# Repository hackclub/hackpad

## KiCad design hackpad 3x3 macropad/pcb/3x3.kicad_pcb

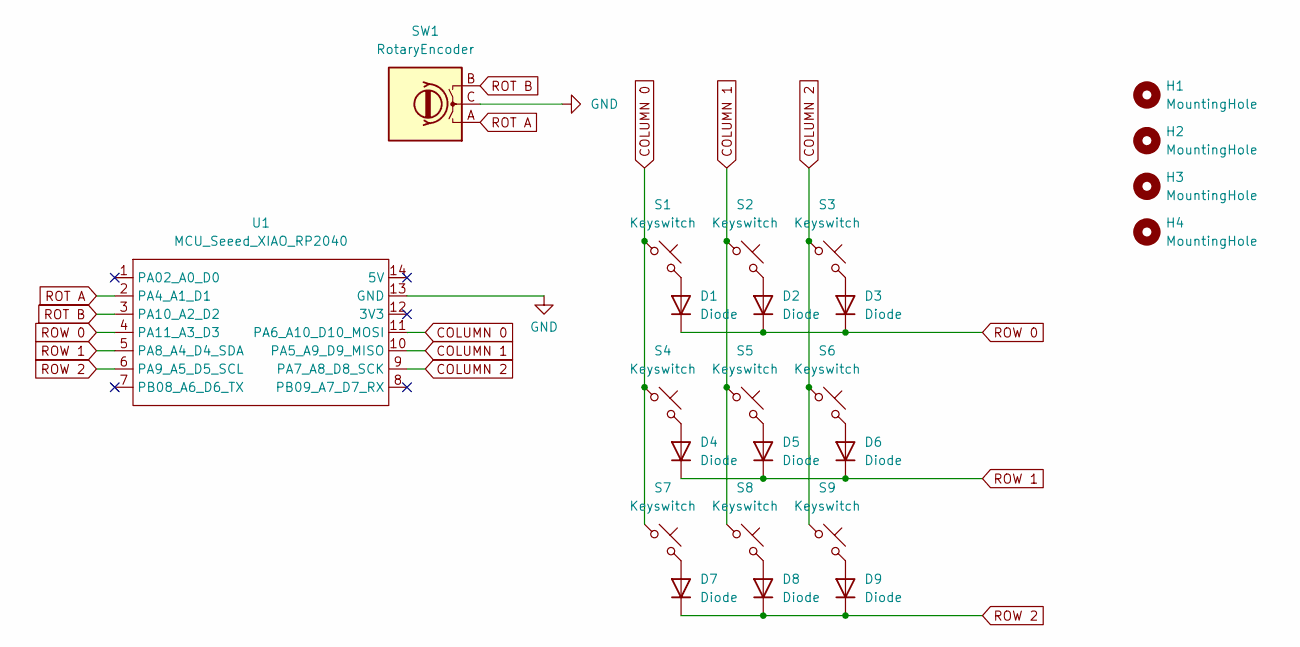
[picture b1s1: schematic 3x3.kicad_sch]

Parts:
D1, D2, D3, D4, D5, D6, D7, D8, D9: Diode; Diode_DO-35
H1, H2, H3, H4: MountingHole; MountingHole_3.5mm
S1, S2, S3, S4, S5, S6, S7, S8, S9: Keyswitch; MX_PCB_1.00u
SW1: RotaryEncoder; RotaryEncoder_Alps_EC11E-Switch_Vertical_H20mm
U1: MCU_Seeed_XIAO_RP2040; Seeed_XIAO_RP2040

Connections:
COLUMN 0: S1.1, S4.1, S7.1, U1.11 (PA6_A10_D10_MOSI)
COLUMN 1: S2.1, S5.1, S8.1, U1.10 (PA5_A9_D9_MISO)
COLUMN 2: S3.1, S6.1, S9.1, U1.9 (PA7_A8_D8_SCK)
GND: SW1.C, U1.13 (GND)
unnamed: D1.2 (A), S1.2
unnamed: D2.2 (A), S2.2
unnamed: D3.2 (A), S3.2
unnamed: D4.2 (A), S4.2
unnamed: D5.2 (A), S5.2
unnamed: D6.2 (A), S6.2
unnamed: D7.2 (A), S7.2
unnamed: D8.2 (A), S8.2
unnamed: D9.2 (A), S9.2
ROT A: SW1.A, U1.2 (PA4_A1_D1)
ROT B: SW1.B, U1.3 (PA10_A2_D2)
ROW 0: D1.1 (K), D2.1 (K), D3.1 (K), U1.4 (PA11_A3_D3)
ROW 1: D4.1 (K), D5.1 (K), D6.1 (K), U1.5 (PA8_A4_D4_SDA)
ROW 2: D7.1 (K), D8.1 (K), D9.1 (K), U1.6 (PA9_A5_D5_SCL)

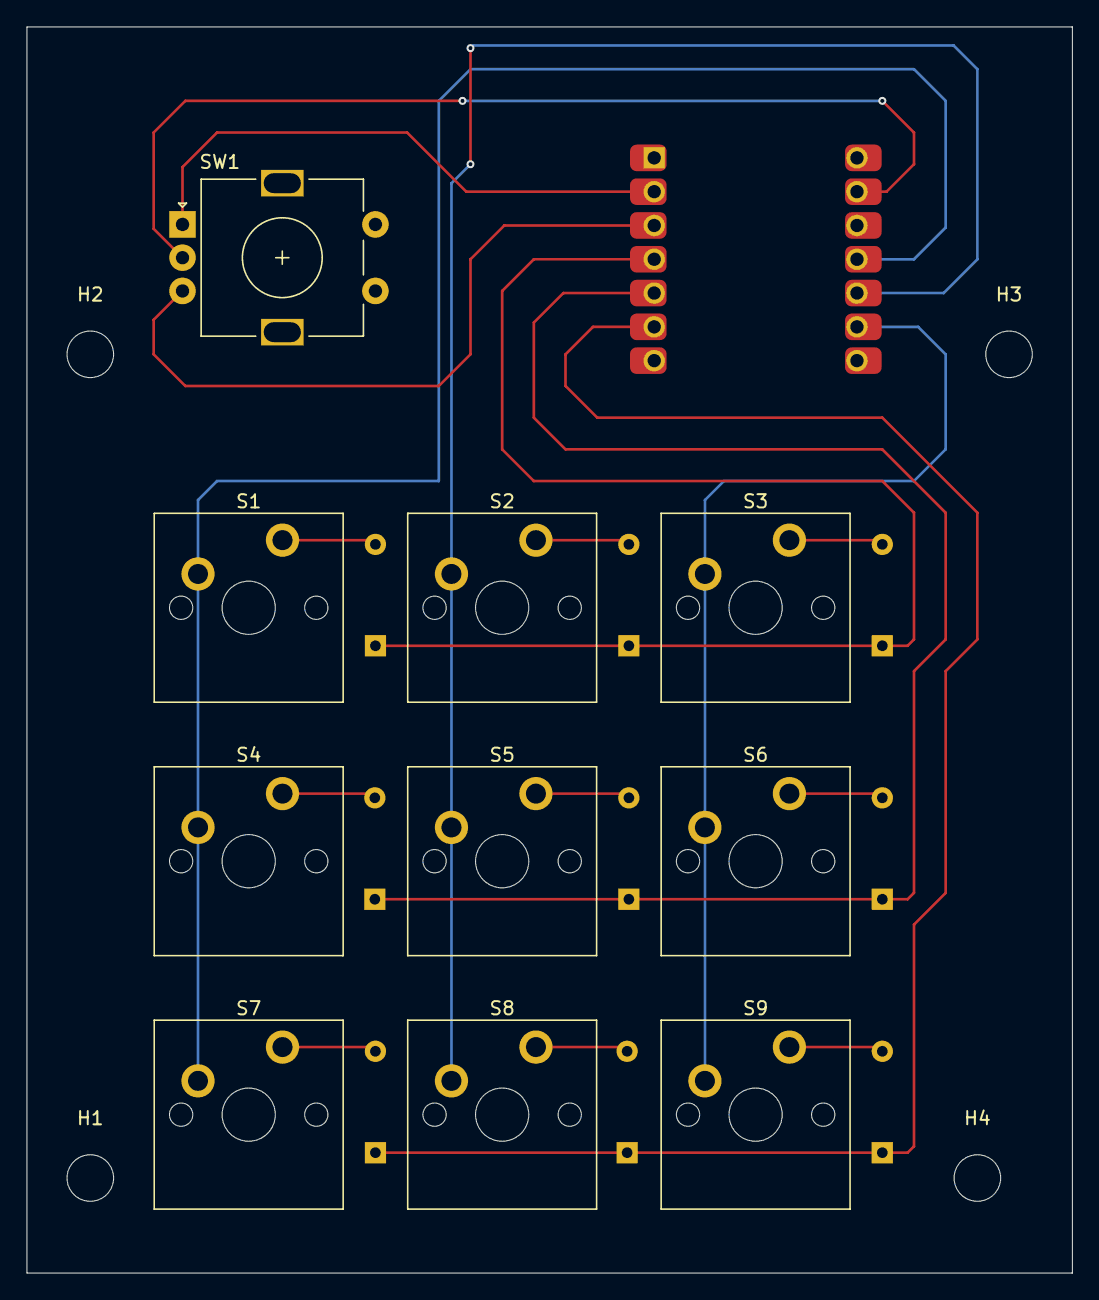
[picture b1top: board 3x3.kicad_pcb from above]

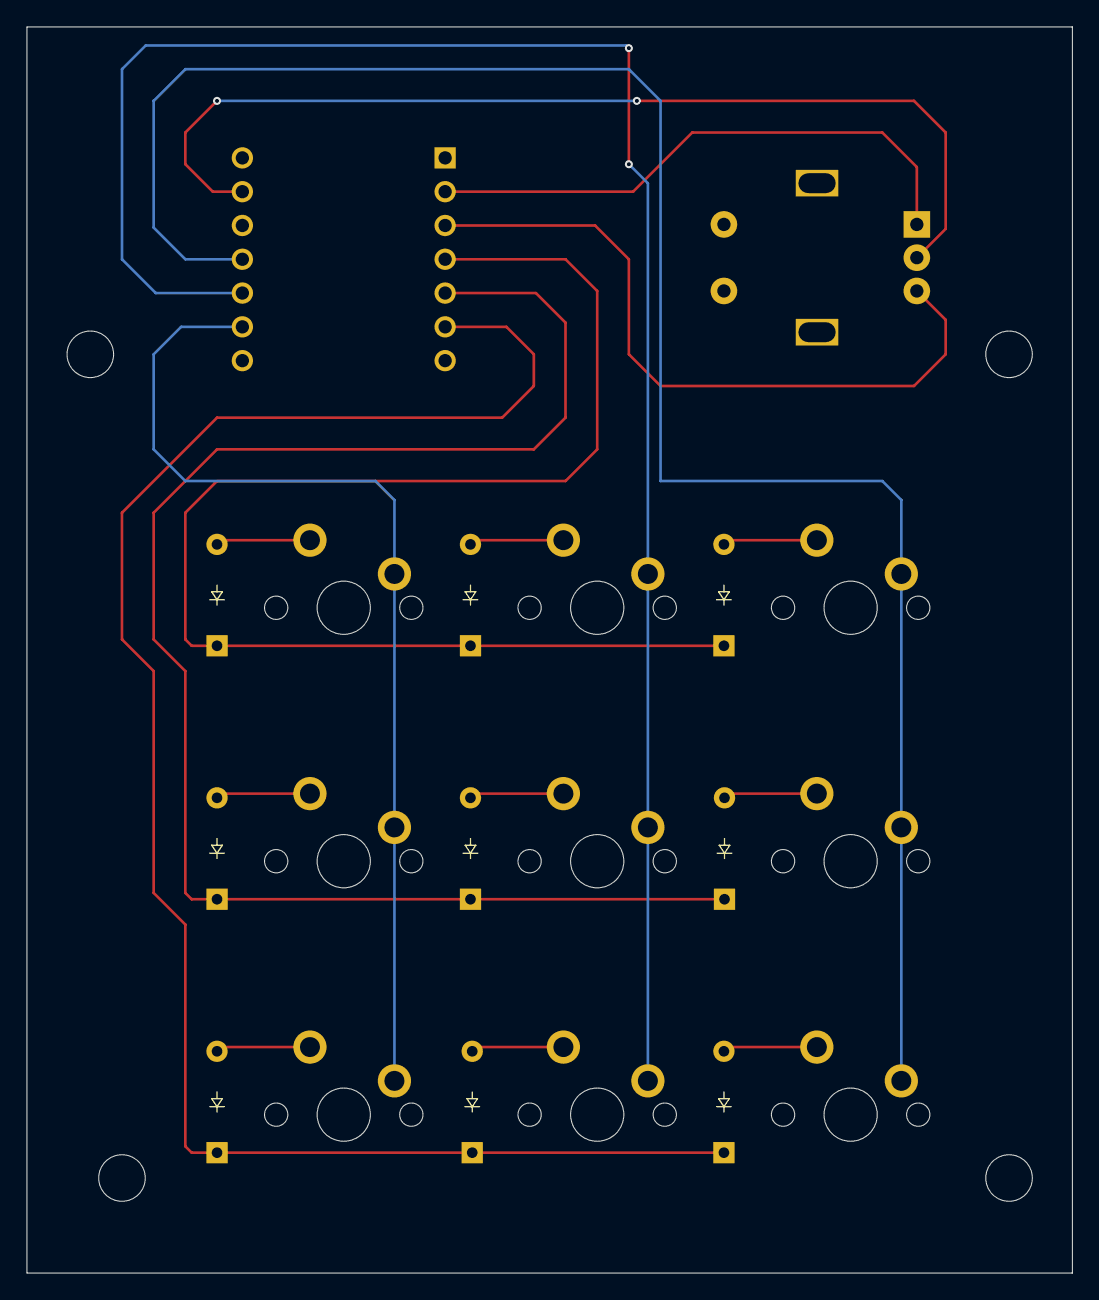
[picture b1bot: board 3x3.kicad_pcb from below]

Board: 2 copper layers, 78.6 x 93.7 mm, 24 parts (9 on the bottom side), 18 nets.

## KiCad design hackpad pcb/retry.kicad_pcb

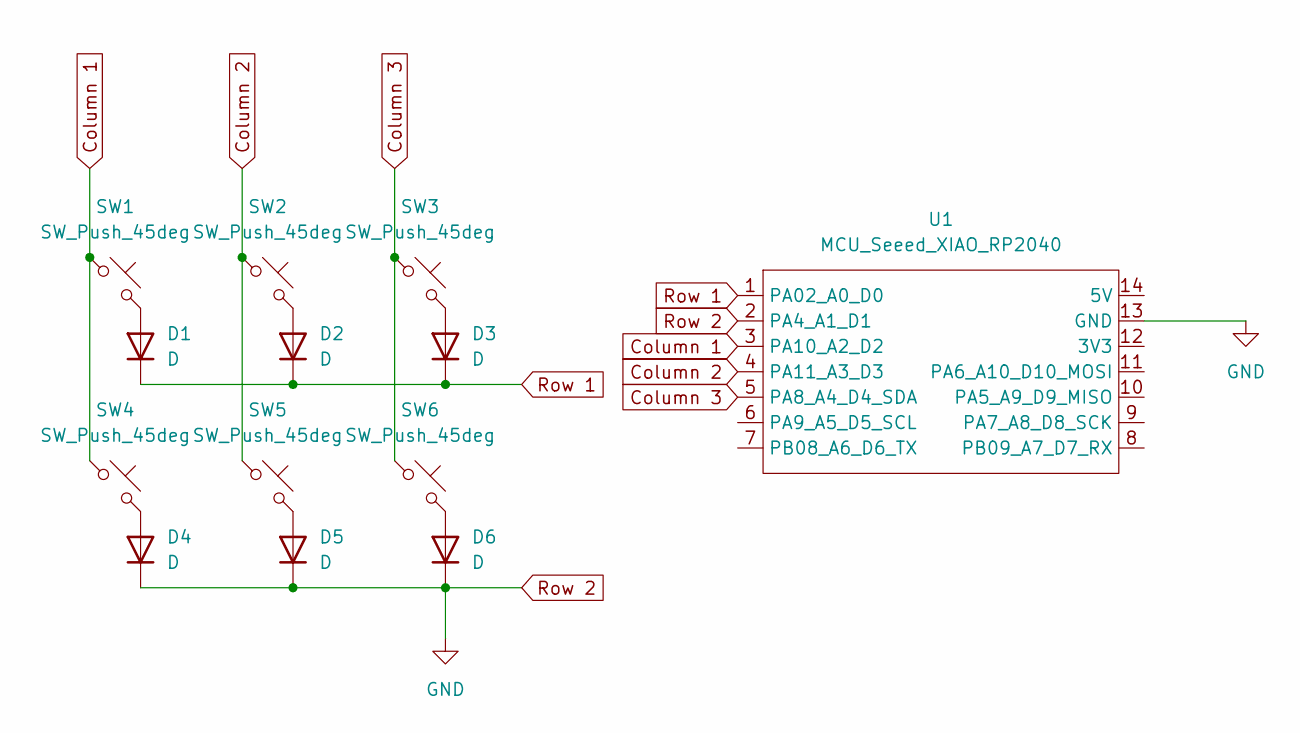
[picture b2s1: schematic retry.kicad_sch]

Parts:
D1, D2, D3, D4, D5, D6: D; Diode_DO-35
SW1, SW2, SW3, SW4, SW5, SW6: SW_Push_45deg; MX_PCB_1.00u
U1: MCU_Seeed_XIAO_RP2040; Seeed_XIAO_RP2040

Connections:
Column 1: SW1.1, SW4.1, U1.3 (PA10_A2_D2)
Column 2: SW2.1, SW5.1, U1.4 (PA11_A3_D3)
Column 3: SW3.1, SW6.1, U1.5 (PA8_A4_D4_SDA)
unnamed: D1.2 (A), SW1.2
unnamed: D2.2 (A), SW2.2
unnamed: D3.2 (A), SW3.2
unnamed: D4.2 (A), SW4.2
unnamed: D5.2 (A), SW5.2
unnamed: D6.2 (A), SW6.2
Row 1: D1.1 (K), D2.1 (K), D3.1 (K), U1.1 (PA02_A0_D0)
Row 2: D4.1 (K), D5.1 (K), D6.1 (K), U1.2 (PA4_A1_D1), U1.13 (GND)

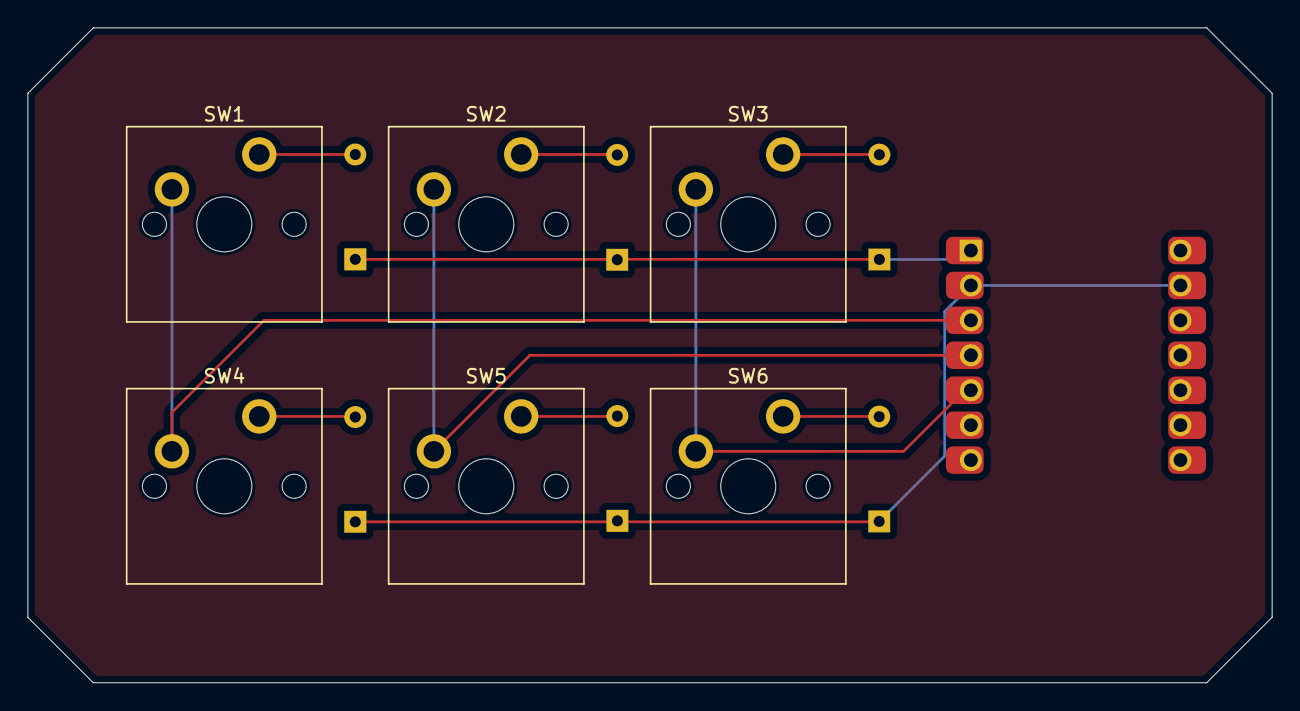
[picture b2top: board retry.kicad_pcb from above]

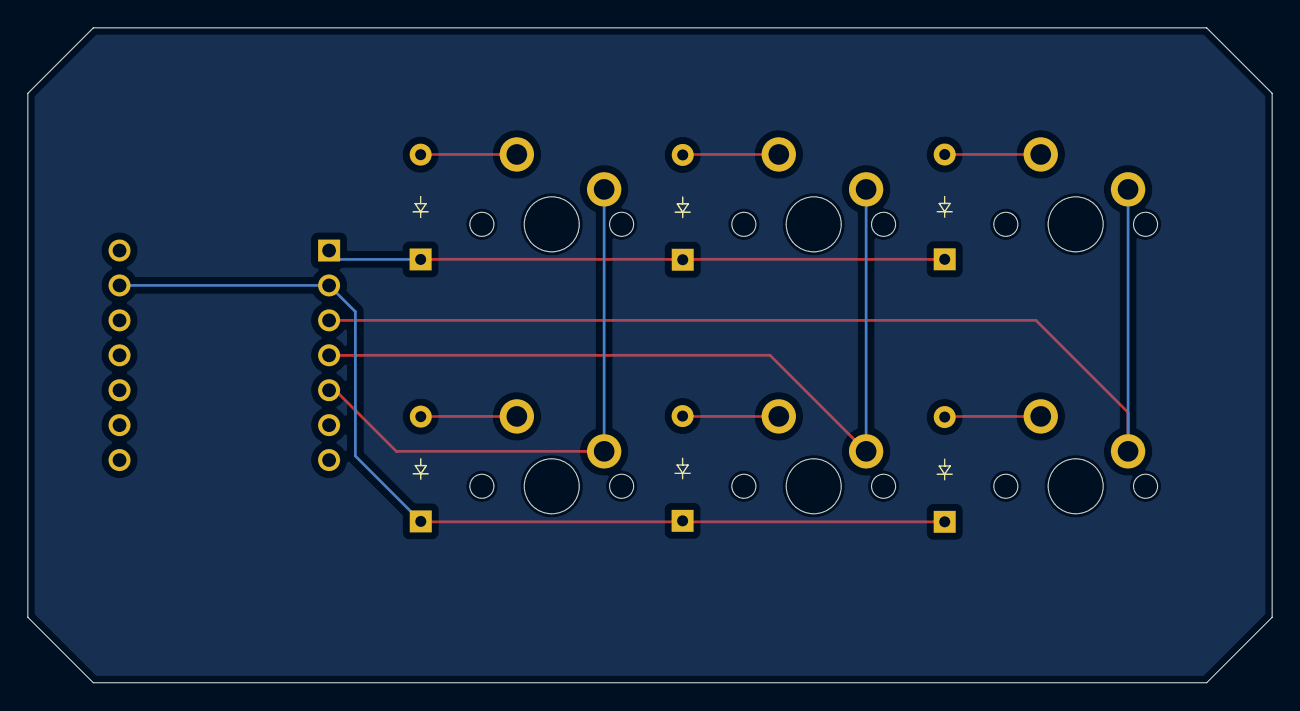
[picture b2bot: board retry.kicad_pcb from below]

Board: 2 copper layers, 90.5 x 47.6 mm, 13 parts (6 on the bottom side), 11 nets.

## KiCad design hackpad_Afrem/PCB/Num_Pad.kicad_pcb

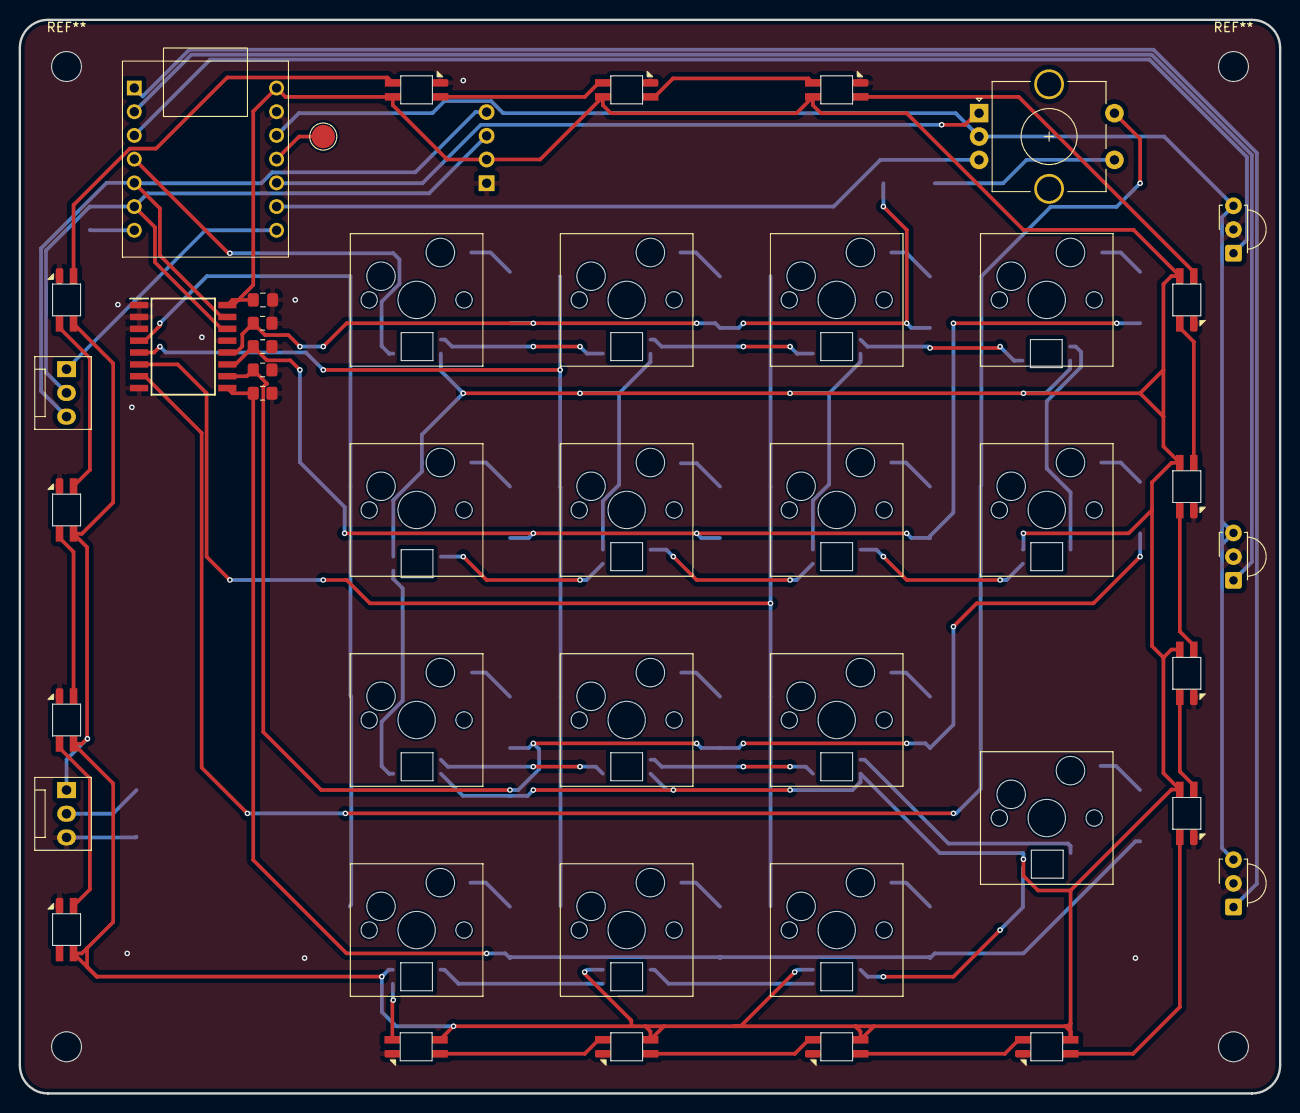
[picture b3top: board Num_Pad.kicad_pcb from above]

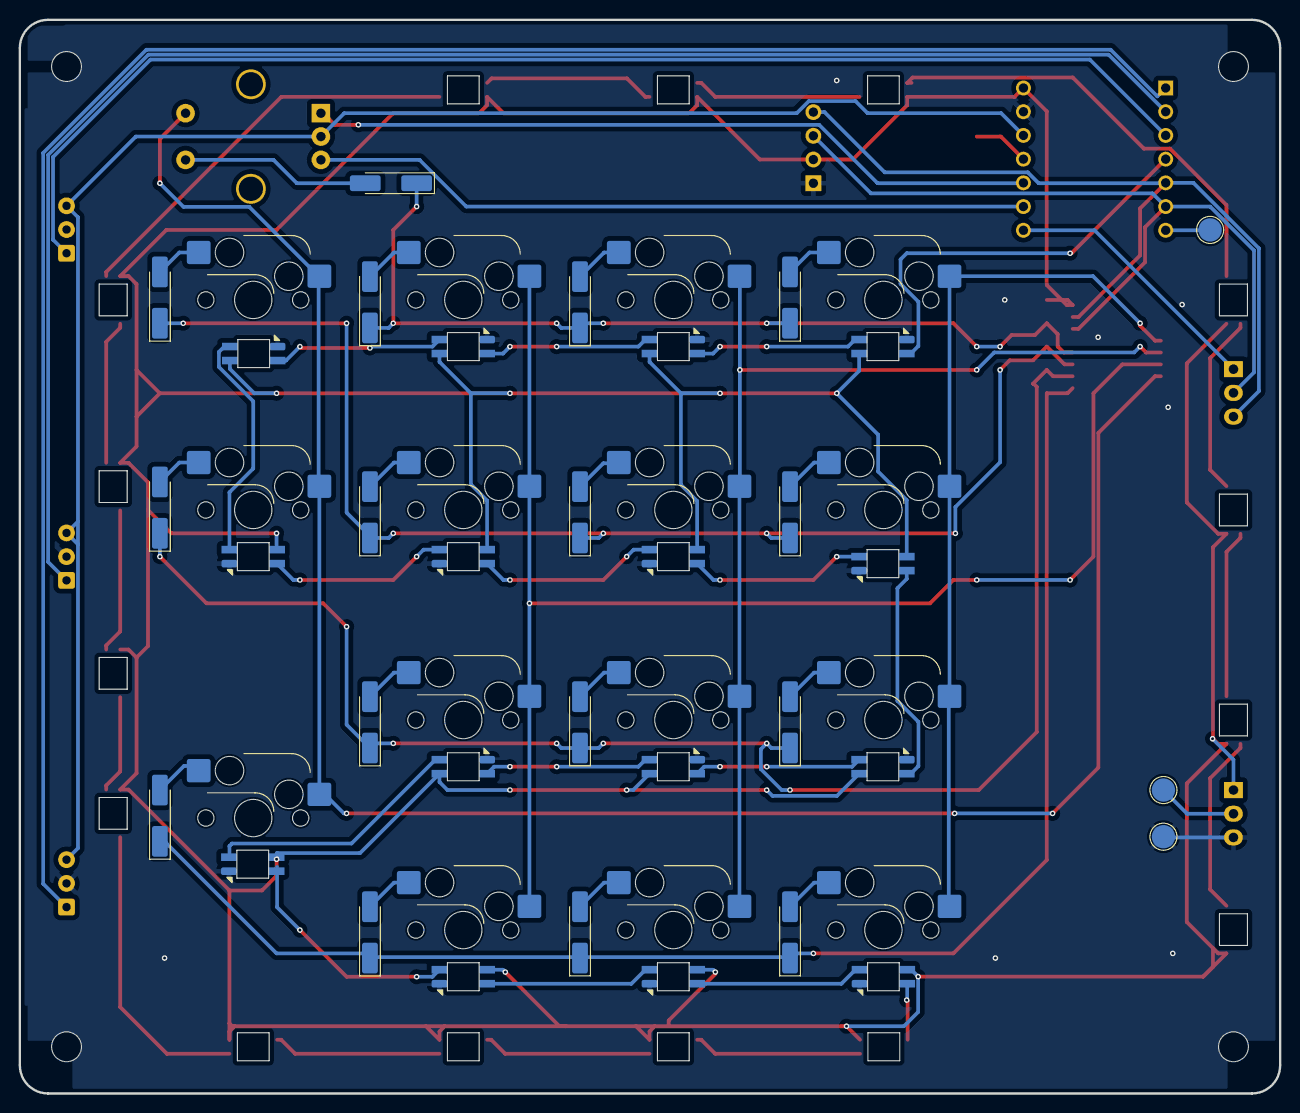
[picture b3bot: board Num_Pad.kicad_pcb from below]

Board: 2 copper layers, 135.0 x 115.0 mm, 79 parts (34 on the bottom side), 68 nets.

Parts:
C1: 100n; C_0805_2012Metric_Pad1.18x1.45mm_HandSolder
D1, D2, D3, D4, D5, D6, D7, D8, D9, D10, D11, D12, D13, D14, D15, D16: Diode; D_MiniMELF_Handsoldering
D19, D20, D21, D22, D23, D24, D25, D26, D27, D28, D29, D30, D31, D32, D33, D34, D35, D36, D37, D38, D39, D40, D41, D42, D43, D44, D45, D46, D47, D48: WS2812B; LED_SK6812MINI
IC1: PCF8574T_3,518; SOIC127P1032X265-16N
J1: OLED_128x32
J3: Data; FanPinHeader_1x03_P2.54mm_Vertical
J4: Spannungsversorgung; FanPinHeader_1x03_P2.54mm_Vertical
R1, R2, R3, R4: 1k; R_0805_2012Metric_Pad1.20x1.40mm_HandSolder
S1: 1; SW_Hotswap_Kailh_MX_1.00u
S2: 2; SW_Hotswap_Kailh_MX_1.00u
S3: 3; SW_Hotswap_Kailh_MX_1.00u
S5: 4; SW_Hotswap_Kailh_MX_1.00u
S6: 5; SW_Hotswap_Kailh_MX_1.00u
S7: 6; SW_Hotswap_Kailh_MX_1.00u
S8: +; SW_Hotswap_Kailh_MX_1.00u
S9: 7; SW_Hotswap_Kailh_MX_1.00u
S10: 8; SW_Hotswap_Kailh_MX_1.00u
S11: 9; SW_Hotswap_Kailh_MX_1.00u
S12: -; SW_Hotswap_Kailh_MX_1.00u
S13: 0; SW_Hotswap_Kailh_MX_1.00u
S14: *; SW_Hotswap_Kailh_MX_1.00u
S15: /; SW_Hotswap_Kailh_MX_1.00u
S16: ENTER; SW_Hotswap_Kailh_MX_2.25u_90deg
SW1: RotaryEncoder_Switch; RotaryEncoder_Alps_EC11E-Switch_Vertical_H20mm_CircularMoun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
TP1, TP2, TP3, TP4: TestPoint; TestPoint_Pad_D2.5mm
U1: MOUDLE-SEEEDUINO-XIAO; MOUDLE14P-2.54-21X17.8MM
U2, U3, U5: TSSP58P38; Vishay_MINICAST-3Pin

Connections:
30kHz: U1.1 (PA02_A0_D0), U2.1 (OUT)
36kHz: U1.2 (PA4_A1_D1), U3.1 (OUT)
56kHz: U1.3 (PA10_A2_D2), U5.1 (OUT)
+3.3V: SW1.C, U1.12 (3V3), U2.3 (Vs), U3.3 (Vs), U5.3 (Vs)
+5V: C1.1, D19.1 (VDD), D20.1 (VDD), D21.1 (VDD), D22.1 (VDD), D23.1 (VDD), D24.1 (VDD), D25.1 (VDD), D26.1 (VDD), D27.1 (VDD), D28.1 (VDD), D29.1 (VDD), D30.1 (VDD), D31.1 (VDD), D32.1 (VDD), D33.1 (VDD), D34.1 (VDD), D35.1 (VDD), D36.1 (VDD), D37.1 (VDD), D38.1 (VDD), D39.1 (VDD), D40.1 (VDD), D41.1 (VDD), D42.1 (VDD), D43.1 (VDD), D44.1 (VDD), D45.1 (VDD), D46.1 (VDD), D47.1 (VDD), D48.1 (VDD), IC1.16 (VDD), J1.2 (VCC), J4.1, U1.14 (5V)
A: SW1.A, U1.10 (PA5_A9_D9_MISO)
B: SW1.B, U1.9 (PA7_A8_D8_SCK)
Col1: IC1.4 (P0), S1.1, S5.1, S9.1, S13.1
Col2: IC1.5 (P1), S2.1, S6.1, S10.1, S14.1
Col3: IC1.6 (P2), S3.1, S7.1, S11.1, S15.1
Col4: IC1.7 (P3), S8.1, S12.1, S16.1, SW1.S2
DIN: D19.4 (DIN), U1.4 (PA11_A3_D3)
GND: C1.2, D19.3 (VSS), D20.3 (VSS), D21.3 (VSS), D22.3 (VSS), D23.3 (VSS), D24.3 (VSS), D25.3 (VSS), D26.3 (VSS), D27.3 (VSS), D28.3 (VSS), D29.3 (VSS), D30.3 (VSS), D31.3 (VSS), D32.3 (VSS), D33.3 (VSS), D34.3 (VSS), D35.3 (VSS), D36.3 (VSS), D37.3 (VSS), D38.3 (VSS), D39.3 (VSS), D40.3 (VSS), D41.3 (VSS), D42.3 (VSS), D43.3 (VSS), D44.3 (VSS), D45.3 (VSS), D46.3 (VSS), D47.3 (VSS), D48.3 (VSS), IC1.1 (A0), IC1.2 (A1), IC1.3 (A2), IC1.8 (VSS), IC1.13 (~INT), J1.1 (GND), J4.3, R1.2, R2.1, R3.2, R4.2, TP1.1, U1.13 (GND), U2.2 (GND), U3.2 (GND), U5.2 (GND)
unnamed: D1.2 (A), S1.2
unnamed: D2.2 (A), S2.2
unnamed: D3.2 (A), S3.2
unnamed: D4.2 (A), SW1.S1
unnamed: D5.2 (A), S5.2
unnamed: D6.2 (A), S6.2
unnamed: D7.2 (A), S7.2
unnamed: D8.2 (A), S8.2
unnamed: D9.2 (A), S9.2
unnamed: D10.2 (A), S10.2
unnamed: D11.2 (A), S11.2
unnamed: D12.2 (A), S12.2
unnamed: D13.2 (A), S13.2
unnamed: D14.2 (A), S14.2
unnamed: D15.2 (A), S15.2
unnamed: D16.2 (A), S16.2
unnamed: D19.2 (DOUT), D20.4 (DIN)
unnamed: D20.2 (DOUT), D21.4 (DIN)
unnamed: D21.2 (DOUT), D22.4 (DIN)
unnamed: D22.2 (DOUT), D23.4 (DIN)
unnamed: D23.2 (DOUT), D24.4 (DIN)
unnamed: D24.2 (DOUT), D25.4 (DIN)
unnamed: D25.2 (DOUT), D26.4 (DIN)
unnamed: D26.2 (DOUT), D27.4 (DIN)
unnamed: D27.2 (DOUT), D28.4 (DIN)
unnamed: D28.2 (DOUT), D29.4 (DIN)
unnamed: D29.2 (DOUT), D30.4 (DIN)
unnamed: D30.2 (DOUT), D31.4 (DIN)
unnamed: D31.2 (DOUT), D32.4 (DIN)
unnamed: D32.2 (DOUT), D33.4 (DIN)
unnamed: D33.2 (DOUT), D34.4 (DIN)
unnamed: D34.2 (DOUT), D35.4 (DIN)
unnamed: D35.2 (DOUT), D36.4 (DIN)
unnamed: D36.2 (DOUT), D37.4 (DIN)
unnamed: D37.2 (DOUT), D38.4 (DIN)
unnamed: D38.2 (DOUT), D39.4 (DIN)
unnamed: D39.2 (DOUT), D40.4 (DIN)
unnamed: D40.2 (DOUT), D41.4 (DIN)
unnamed: D41.2 (DOUT), D42.4 (DIN)
unnamed: D42.2 (DOUT), D43.4 (DIN)
unnamed: D43.2 (DOUT), D44.4 (DIN)
unnamed: D44.2 (DOUT), D45.4 (DIN)
unnamed: D45.2 (DOUT), D46.4 (DIN)
unnamed: D46.2 (DOUT), D47.4 (DIN)
unnamed: D47.2 (DOUT), D48.4 (DIN)
unnamed: J4.2, TP3.1
unnamed: TP2.1, U1.11 (PA6_A10_D10_MOSI)
unnamed: TP4.1, U1.7 (PB08_A6_D6_TX)
Row 1: D1.1 (K), D2.1 (K), D3.1 (K), D4.1 (K), IC1.12 (P7), R1.1
Row 2: D5.1 (K), D6.1 (K), D7.1 (K), D8.1 (K), IC1.11 (P6), R2.2
Row 3: D9.1 (K), D10.1 (K), D11.1 (K), D12.1 (K), IC1.10 (P5), R3.1
Row 4: D13.1 (K), D14.1 (K), D15.1 (K), D16.1 (K), IC1.9 (P4), R4.1
SCL: IC1.14 (SCL), J1.3 (SCL), J3.2, U1.6 (PA9_A5_D5_SCL)
SDA: IC1.15 (SDA), J1.4 (SDA), J3.3, U1.5 (PA8_A4_D4_SDA)
con: J3.1, U1.8 (PB09_A7_D7_RX)

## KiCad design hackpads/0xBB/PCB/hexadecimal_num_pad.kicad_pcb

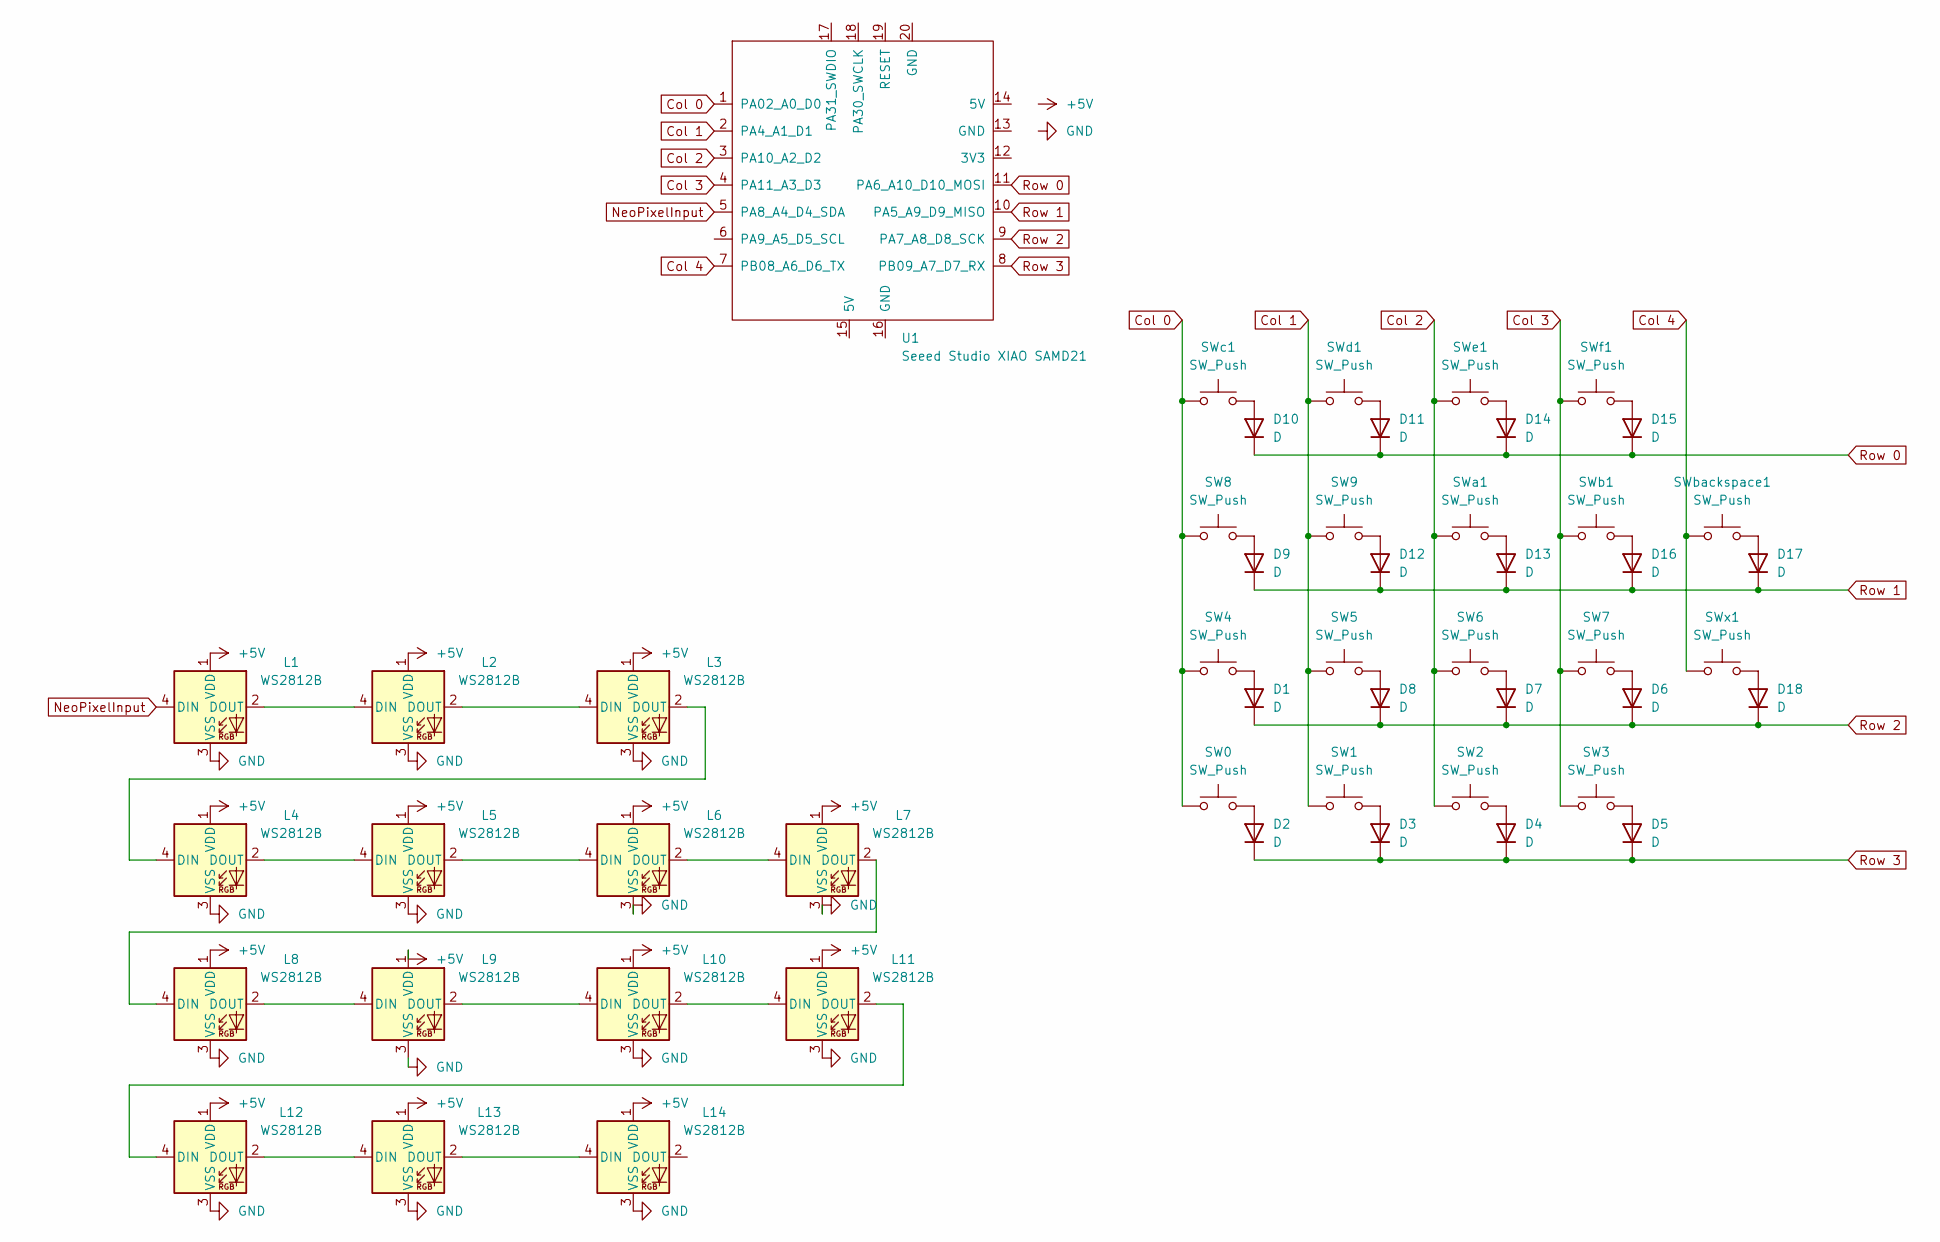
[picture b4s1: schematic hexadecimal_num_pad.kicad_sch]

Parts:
D1, D2, D3, D4, D5, D6, D7, D8, D9, D10, D11, D12, D13, D14, D15, D16, D17, D18: D; D_DO-35_SOD27_P7.62mm_Horizontal
L1, L2, L3, L4, L5, L6, L7, L8, L9, L10, L11, L12, L13, L14: WS2812B; LED_WS2812B_PLCC4_5.0x5.0mm_P3.2mm
SW0, SW1, SW2, SW3, SW4, SW5, SW6, SW7, SW8, SW9: SW_Push; SW_Cherry_MX_1.00u_PCB
SWa1: SW_Push; SW_Cherry_MX_1.00u_PCB
SWb1: SW_Push; SW_Cherry_MX_1.00u_PCB
SWbackspace1: SW_Push; SW_Cherry_MX_1.00u_PCB
SWc1: SW_Push; SW_Cherry_MX_1.00u_PCB
SWd1: SW_Push; SW_Cherry_MX_1.00u_PCB
SWe1: SW_Push; SW_Cherry_MX_1.00u_PCB
SWf1: SW_Push; SW_Cherry_MX_1.00u_PCB
SWx1: SW_Push; SW_Cherry_MX_1.00u_PCB
U1: Seeed Studio XIAO SAMD21; XIAO-Generic-Thruhole-14P-2.54-21X17.8MM

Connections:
+5V: L1.1 (VDD), L2.1 (VDD), L3.1 (VDD), L4.1 (VDD), L5.1 (VDD), L6.1 (VDD), L7.1 (VDD), L8.1 (VDD), L9.1 (VDD), L10.1 (VDD), L11.1 (VDD), L12.1 (VDD), L13.1 (VDD), L14.1 (VDD)
Col 0: SW0.1, SW4.1, SW8.1, SWc1.1, U1.1 (PA02_A0_D0)
Col 1: SW1.1, SW5.1, SW9.1, SWd1.1, U1.2 (PA4_A1_D1)
Col 2: SW2.1, SW6.1, SWa1.1, SWe1.1, U1.3 (PA10_A2_D2)
Col 3: SW3.1, SW7.1, SWb1.1, SWf1.1, U1.4 (PA11_A3_D3)
Col 4: SWbackspace1.1, SWx1.1, U1.7 (PB08_A6_D6_TX)
GND: L1.3 (VSS), L2.3 (VSS), L3.3 (VSS), L4.3 (VSS), L5.3 (VSS), L6.3 (VSS), L7.3 (VSS), L8.3 (VSS), L9.3 (VSS), L10.3 (VSS), L11.3 (VSS), L12.3 (VSS), L13.3 (VSS), L14.3 (VSS)
NeoPixelInput: L1.4 (DIN), U1.5 (PA8_A4_D4_SDA)
unnamed: D1.2 (A), SW4.2
unnamed: D2.2 (A), SW0.2
unnamed: D3.2 (A), SW1.2
unnamed: D4.2 (A), SW2.2
unnamed: D5.2 (A), SW3.2
unnamed: D6.2 (A), SW7.2
unnamed: D7.2 (A), SW6.2
unnamed: D8.2 (A), SW5.2
unnamed: D9.2 (A), SW8.2
unnamed: D10.2 (A), SWc1.2
unnamed: D11.2 (A), SWd1.2
unnamed: D12.2 (A), SW9.2
unnamed: D13.2 (A), SWa1.2
unnamed: D14.2 (A), SWe1.2
unnamed: D15.2 (A), SWf1.2
unnamed: D16.2 (A), SWb1.2
unnamed: D17.2 (A), SWbackspace1.2
unnamed: D18.2 (A), SWx1.2
unnamed: L1.2 (DOUT), L2.4 (DIN)
unnamed: L2.2 (DOUT), L3.4 (DIN)
unnamed: L3.2 (DOUT), L4.4 (DIN)
unnamed: L4.2 (DOUT), L5.4 (DIN)
unnamed: L5.2 (DOUT), L6.4 (DIN)
unnamed: L6.2 (DOUT), L7.4 (DIN)
unnamed: L7.2 (DOUT), L8.4 (DIN)
unnamed: L8.2 (DOUT), L9.4 (DIN)
unnamed: L9.2 (DOUT), L10.4 (DIN)
unnamed: L10.2 (DOUT), L11.4 (DIN)
unnamed: L11.2 (DOUT), L12.4 (DIN)
unnamed: L12.2 (DOUT), L13.4 (DIN)
unnamed: L13.2 (DOUT), L14.4 (DIN)
Row 0: D10.1 (K), D11.1 (K), D14.1 (K), D15.1 (K), U1.11 (PA6_A10_D10_MOSI)
Row 1: D9.1 (K), D12.1 (K), D13.1 (K), D16.1 (K), D17.1 (K), U1.10 (PA5_A9_D9_MISO)
Row 2: D1.1 (K), D6.1 (K), D7.1 (K), D8.1 (K), D18.1 (K), U1.9 (PA7_A8_D8_SCK)
Row 3: D2.1 (K), D3.1 (K), D4.1 (K), D5.1 (K), U1.8 (PB09_A7_D7_RX)

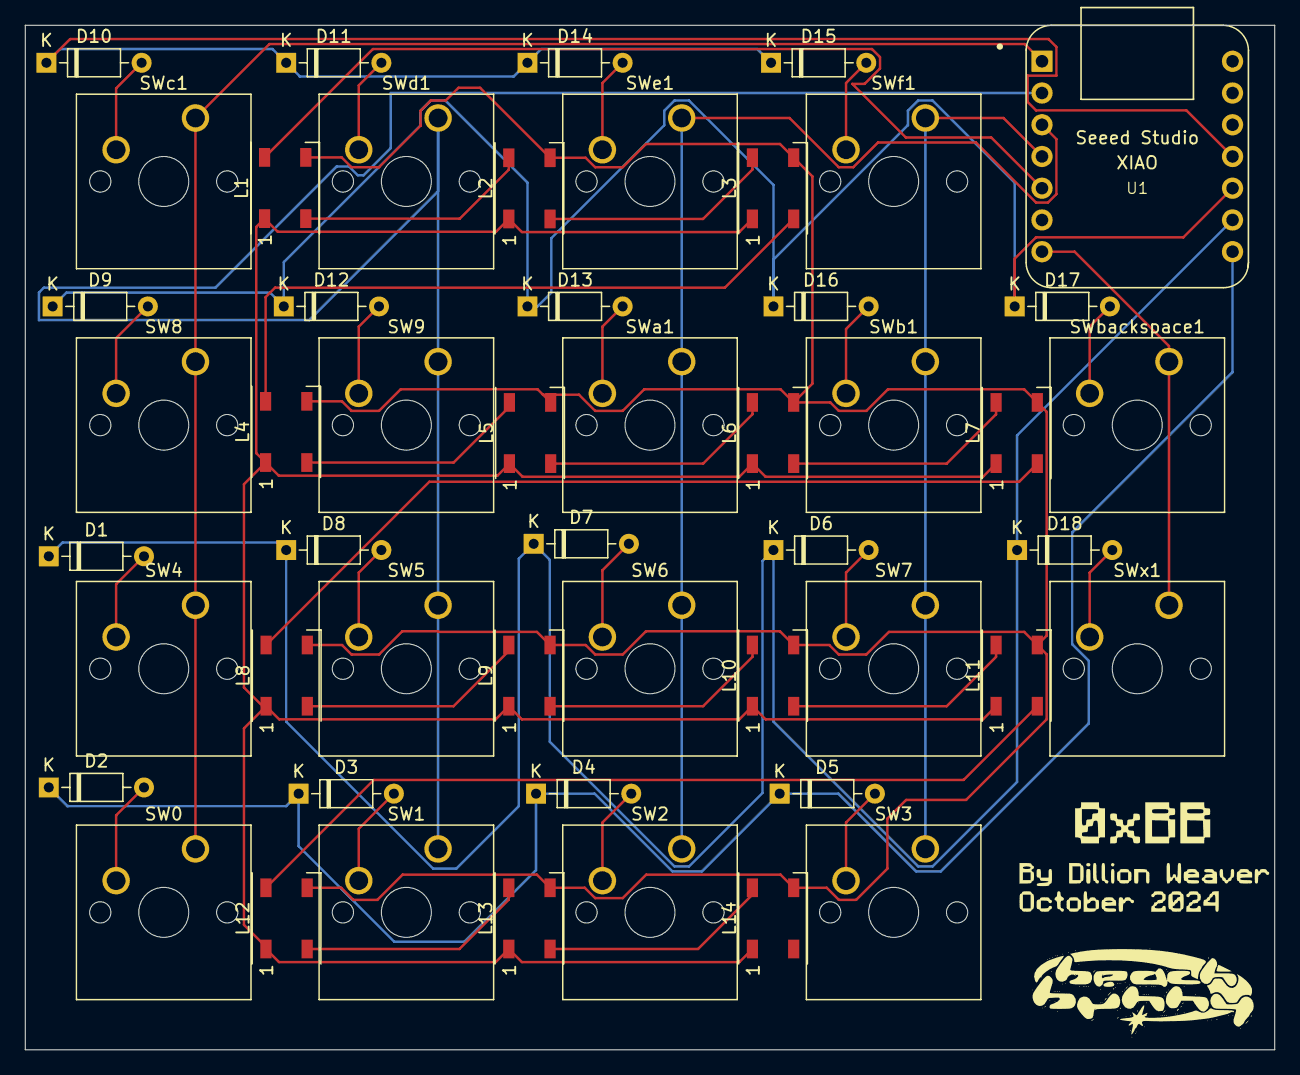
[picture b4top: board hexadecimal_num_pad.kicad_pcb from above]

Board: 2 copper layers, 100.0 x 82.0 mm, 51 parts (0 on the bottom side), 43 nets.

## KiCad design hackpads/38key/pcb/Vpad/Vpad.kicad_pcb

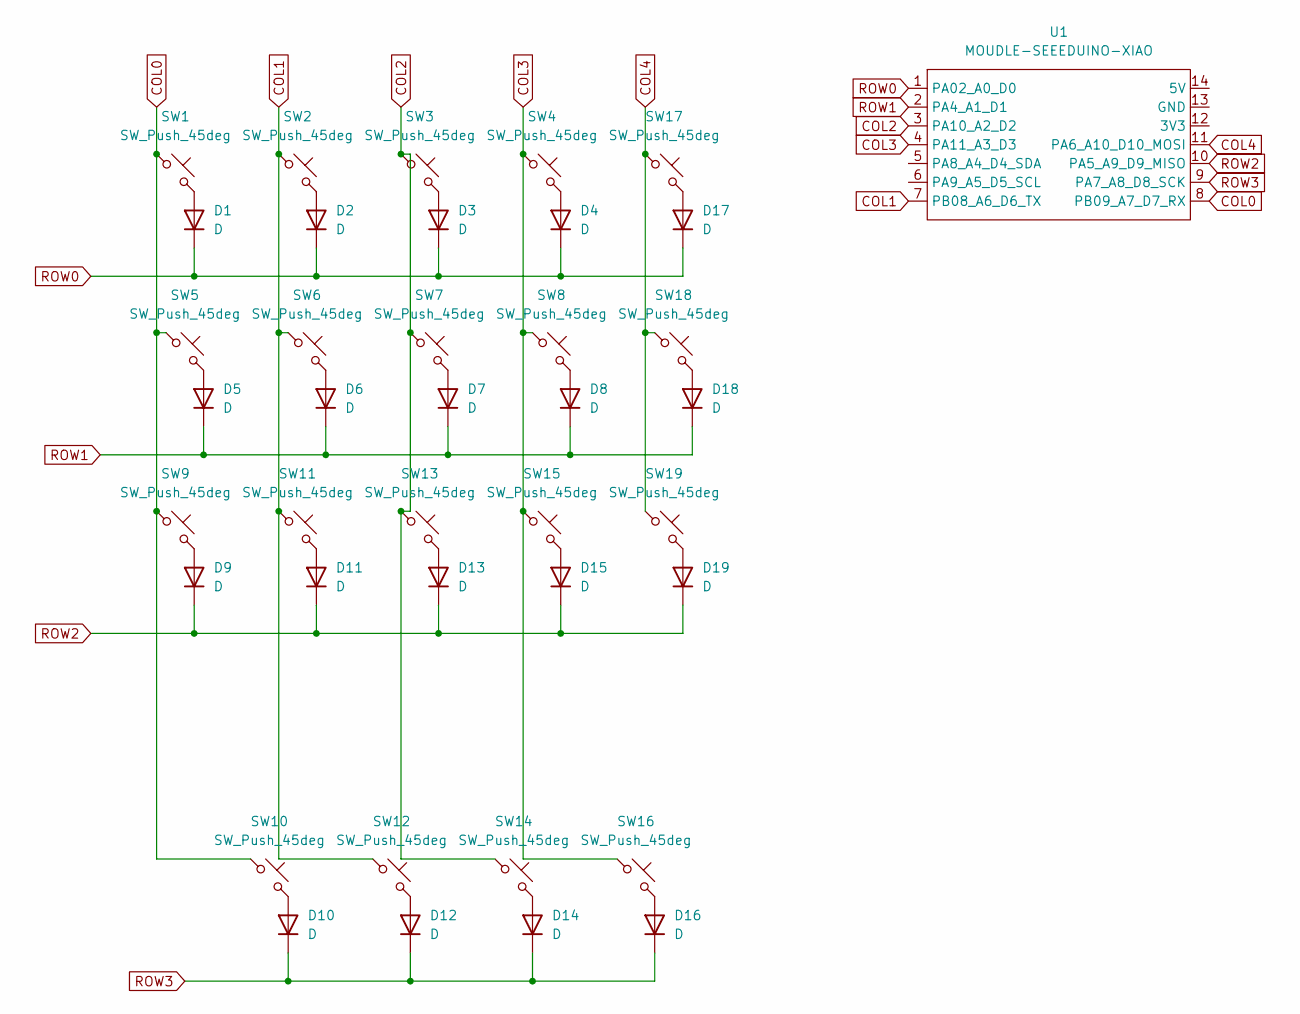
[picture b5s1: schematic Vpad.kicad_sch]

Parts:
D1, D2, D3, D4, D5, D6, D7, D8, D9, D10, D11, D12, D13, D14, D15, D16, D17, D18, D19: D; D_DO-35_SOD27_P7.62mm_Horizontal
SW1, SW2, SW3, SW4, SW5, SW6, SW7, SW8, SW9, SW10, SW11, SW12, SW13, SW14, SW15, SW16, SW17, SW18: SW_Push_45deg; Choc_V1V2_1.00u
SW19: SW_Push_45deg; Choc_V1V2_1.50u_90deg
U1: MOUDLE-SEEEDUINO-XIAO; XIAO-Generic-Thruhole-14P-2.54-21X17.8MM

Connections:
COL0: SW1.1, SW5.1, SW9.1, SW10.1, U1.8 (PB09_A7_D7_RX)
COL1: SW2.1, SW6.1, SW11.1, SW12.1, U1.7 (PB08_A6_D6_TX)
COL2: SW3.1, SW7.1, SW13.1, SW14.1, U1.3 (PA10_A2_D2)
COL3: SW4.1, SW8.1, SW15.1, SW16.1, U1.4 (PA11_A3_D3)
COL4: SW17.1, SW18.1, SW19.1, U1.11 (PA6_A10_D10_MOSI)
unnamed: D1.2 (A), SW1.2
unnamed: D2.2 (A), SW2.2
unnamed: D3.2 (A), SW3.2
unnamed: D4.2 (A), SW4.2
unnamed: D5.2 (A), SW5.2
unnamed: D6.2 (A), SW6.2
unnamed: D7.2 (A), SW7.2
unnamed: D8.2 (A), SW8.2
unnamed: D9.2 (A), SW9.2
unnamed: D10.2 (A), SW10.2
unnamed: D11.2 (A), SW11.2
unnamed: D12.2 (A), SW12.2
unnamed: D13.2 (A), SW13.2
unnamed: D14.2 (A), SW14.2
unnamed: D15.2 (A), SW15.2
unnamed: D16.2 (A), SW16.2
unnamed: D17.2 (A), SW17.2
unnamed: D18.2 (A), SW18.2
unnamed: D19.2 (A), SW19.2
ROW0: D1.1 (K), D2.1 (K), D3.1 (K), D4.1 (K), D17.1 (K), U1.1 (PA02_A0_D0)
ROW1: D5.1 (K), D6.1 (K), D7.1 (K), D8.1 (K), D18.1 (K), U1.2 (PA4_A1_D1)
ROW2: D9.1 (K), D11.1 (K), D13.1 (K), D15.1 (K), D19.1 (K), U1.10 (PA5_A9_D9_MISO)
ROW3: D10.1 (K), D12.1 (K), D14.1 (K), D16.1 (K), U1.9 (PA7_A8_D8_SCK)
